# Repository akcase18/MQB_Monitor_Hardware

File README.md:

# Hardware Design for MQB Monitor

This is the PCB used for my software project, MQB Monitor, and enables the software features found in that repository.

This project was fully designed in KiCad, with the intention of using JLCPCB for both PCB manufacturing and assembly.

## Features

This project was designed to be a full plug-and-play compact display that could be used to show configurable information as reported by my car. I wanted installation to be easy and fully reversible, and require little-to-know technical knowledge in order to get it up and running.

To support this goal, this PCB is designed around a 480x320 3.5" LCD panel that supports capacitive touch, fast refresh rates, high-brightess, and is readily available. This allows the screen to be visible in a car in all but direct sunlight, react quickly to new information, and is glass-coated for better durablility and easier use. The PCB attaches directly to the back of the LCD panel (I use double-sided tape) for a secure and very compact package.

It utilizes a 4-wire connection to the car with a custom wiring harness that plugs directly into the OBD2 port. It pulls power, ground, and CAN (CAN high and low) directly from the port. Power is pulled from the ignition source, so the display turns on when the car turns on, turns off when the car turns off, and doesn't pull power while the car is off so there is no extra battey drain.

It also has a USB-C port on-board that can be used for updates and other communication with the MCU.

## Major Components

The full BOM can be found in the KiCad project, as well as in the `bom_production` folder, but the major components used for this are listed below. Please note, this information is only applicable to PCB v5.1.0.

- ESP32-S3-WROOM-1: This is the MCU for the project, and is what actually runs the display. For this board, it is recommended to use N16R8. See below for a more in-depth explanation.
  - There are multiple different flash configurations for this ESP module, indicated using N{X}R{Y}, where X is total flash storage and Y is the amount of PSRAM in the module. On v5.0.2 of this board, only N16R2 was supported because 1) N16 gives you maximum internal flash for logging purposes and 2) R2 uses quad SPI for PSRAM instead of octal SPI (which is used by other R configurations). THe pinout used for that PCB was not compatible with octal SPI PSRAM.
- PAM2804AAB010: LCD backlight driver. Used to control display brightness.
- PLMR54410DBVR: 12v -> 5v switching regulator, helps with overvoltage protection when connected to the car as well.
- AMS1117-3.3L: 5v -> 3.3v LDO, provides steady voltage source for display and MCU.
- SN65HVD230: Automotive CAN transceiver.
- ER-TFT035-6: LCD panel used. This connects to the PCB via 50-pin FPC connector, has a capacitive touch controller (via I2c), and is driven by the MCU using 8-bit parallel.

As mentioned, there are other supporting components used that are listed in the full BOM. There may be alternatives to some of the components on the board, but the components selected were chosen to minimize cost and maximize component availablilty, specifically for using JLCPCB for PCBA.

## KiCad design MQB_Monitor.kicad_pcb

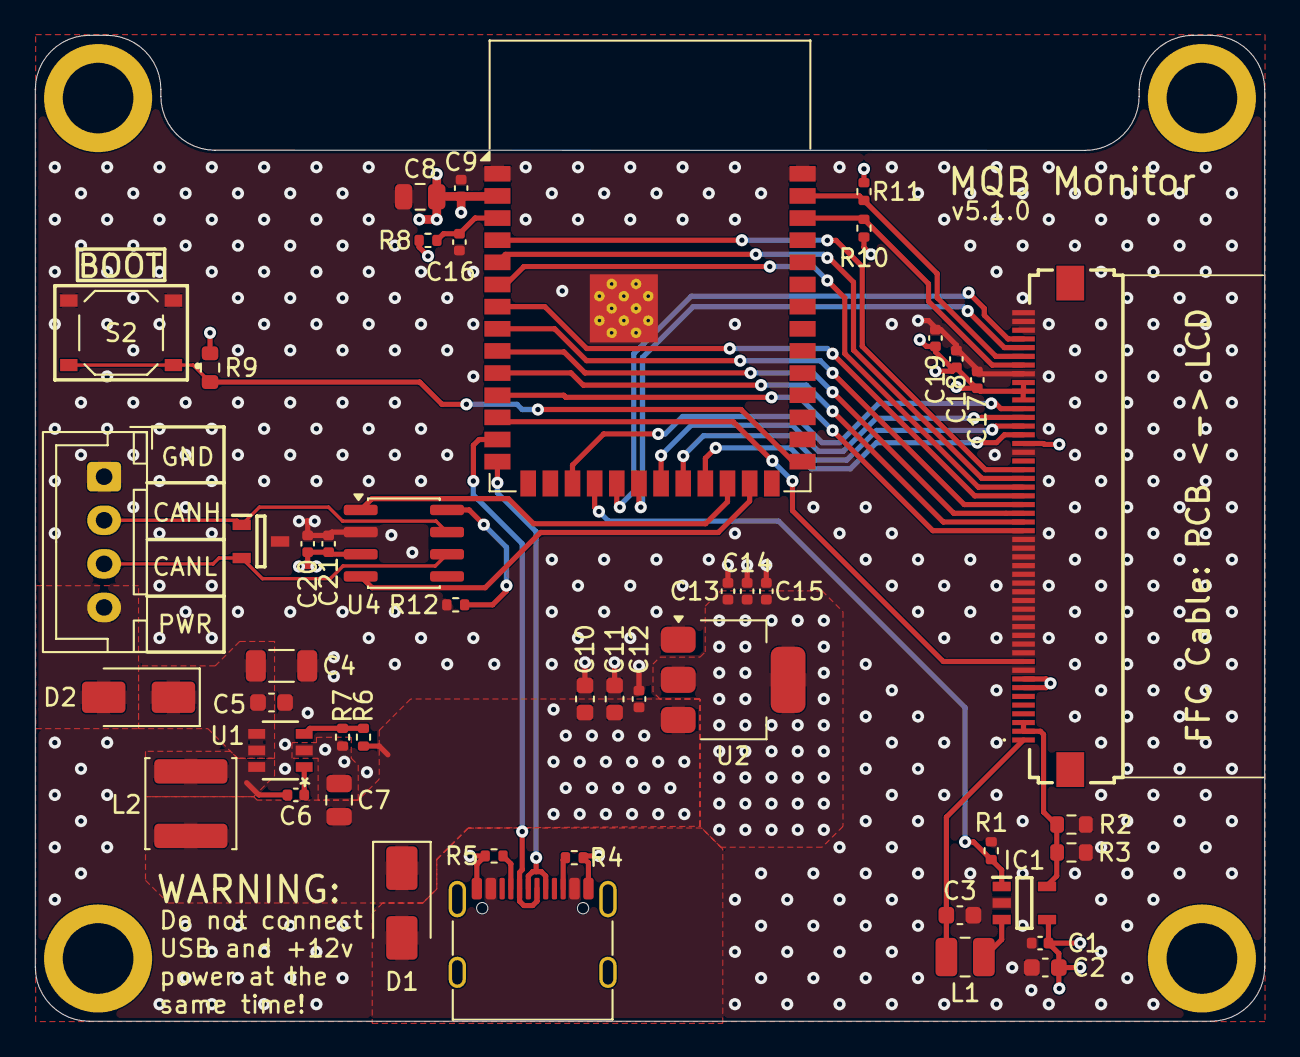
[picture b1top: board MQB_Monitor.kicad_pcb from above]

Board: 4 copper layers, 70.5 x 56.5 mm, 51 parts (0 on the bottom side), 41 nets.

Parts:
C1, C6, C9, C12, C13, C17, C18, C21: 0.1uF; C_0402_1005Metric
C2, C3, C10, C11: 10uF; C_0603_1608Metric
C4: 10uF; C_1206_3216Metric
C5: 0.1uF; C_0603_1608Metric
C7, C8: 22uF; C_0805_2012Metric
C14, C15, C19, C20: 10uF; C_0402_1005Metric
C16: 1uF; C_0402_1005Metric
D1, D2: Diode; D_SMA
D3: PESD1CAN,215; SOT95P230X110-3N
H1, H2, H3, H4: MountingHole; Keystone_24881
IC1: PAM2804AAB010; SOT95P280X100-5N
J1: AFC01-S50FCA-00; AFC01S50FCA00
J2: 4-Pin to Car; JST_XH_B4B-XH-A_1x04_P2.50mm_Vertical
L1: 4.7uH; L_1008_2520Metric
L2: 15uH; L_Changjiang_FNR5040S
R1: 100k; R_0402_1005Metric
R2: 1R; R_0603_1608Metric
R3: 10R; R_0603_1608Metric
R4, R5: 5.1k; R_0402_1005Metric
R6: 51k; R_0402_1005Metric
R7, R8, R10, R11, R12: 10k; R_0402_1005Metric
R9: 1k; R_0603_1608Metric
S2: Push Button; SW_PTS526_SM08_SMTR2_LFS
U1: PLMR54410DBVR; U_SOT-23_TEX
U2: AMS1117-3.3; SOT-223-3_TabPin2
U3: ESP32-S3-WROOM-1
U4: SN65HVD230; SOIC-8_3.9x4.9mm_P1.27mm
USB1: USB-C Port; USB_C_Receptacle_G-Switch_GT-USB-7010ASV

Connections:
+3.3V: C8.1, C9.1, C13.1, C14.1, C15.1, C17.1, C18.1, C19.1, C20.1, C21.1, J1.7, J1.8, J1.35, J1.40, J1.41, J1.42, R8.2, R9.1, R10.1, R11.1, U2.2 (VO), U3.2 (3V3), U4.3 (VCC)
+5V: C1.1, C2.1, C7.1, C10.1, C11.1, C12.1, D1.1 (K), IC1.4 (VIN), L2.1, R6.1, U2.3 (VI)
+12V: C4.1, C5.1, D2.1 (K), U1.4 (EN), U1.5 (VIN)
/12V_Car: D2.2 (A), J2.4
/CAN_RS: R12.1, U4.8 (Rs)
/CB: C6.2, U1.1 (CB)
/ESP_BOOT: R9.2, S2.1, S2.2, U3.27 (IO0)
/ESP_EN: C16.2, R8.1, U3.3 (EN)
/FB: R6.2, R7.1, U1.3 (FB)
/P1_CC1: R5.1, USB1.A5 (CC1)
/P1_CC2: R4.2, USB1.B5 (CC2)
/P1_VBUS: D1.2 (A), USB1.A4 (VBUS), USB1.A9 (VBUS), USB1.B4 (VBUS), USB1.B9 (VBUS)
/SW: C6.1, L2.2, U1.6 (SW)
BL_CTRL: IC1.1 (EN), R1.1, U3.18 (IO10)
CANH: D3.1 (CATHODE_1), J2.2, U4.7 (CANH)
CANL: D3.2 (CATHODE_2), J2.3, U4.6 (CANL)
CAN_RXI: U3.25 (IO48), U4.4 (R)
CAN_TX0: U3.24 (IO47), U4.1 (D)
ESP_USB_N: U3.13 (USB_D-), USB1.A7 (D-), USB1.B7 (D-)
ESP_USB_P: U3.14 (USB_D+), USB1.A6 (D+), USB1.B6 (D+)
GND: C1.2, C2.2, C3.2, C4.2, C5.2, C7.2, C8.2, C9.2, C10.2, C11.2, C12.2, C13.2, C14.2, C15.2, C16.1, C17.2, C18.2, C19.2, C20.2, C21.2, D3.3 (COMMON_CATHODE), IC1.2 (GND), J1.9, J1.11, J1.12, J1.13, J1.14, J1.15, J1.16, J1.17, J1.18, J1.19, J1.20, J1.21, J1.22, J1.23, J1.24, J1.34, J1.43, J1.48, J1.49, J1.50, J2.1, R1.2, R2.2, R3.2, R4.1, R5.2, R7.2, R12.2, S2.3, S2.4, U1.2 (GND), U2.1 (GND), U3.1 (GND), U3.40 (GND), U3.41 (GND), U4.2 (GND), USB1.A1 (GND), USB1.A12 (GND), USB1.B1 (GND), USB1.B12 (GND)
LCD_CS: J1.38, U3.21 (IO13)
LCD_DC: J1.37, U3.22 (IO14)
LCD_RESET: J1.10, U3.12 (IO8)
LCD_TE: J1.39, U3.17 (IO9)
LCD_WR: J1.36, U3.23 (IO21)
LED_A: C3.1, J1.1, L1.2
LED_K: IC1.5 (VOUT/FB), J1.2, J1.3, R2.1, R3.1
unnamed: IC1.3 (SW), L1.1
PARALLEL_0: J1.32, U3.4 (IO4)
PARALLEL_1: J1.31, U3.5 (IO5)
PARALLEL_2: J1.30, U3.6 (IO6)
PARALLEL_3: J1.29, U3.7 (IO7)
PARALLEL_4: J1.28, U3.8 (IO15)
PARALLEL_5: J1.27, U3.9 (IO16)
PARALLEL_6: J1.26, U3.10 (IO17)
PARALLEL_7: J1.25, U3.11 (IO18)
TOUCH_PEN_INT: J1.46, U3.20 (IO12)
TOUCH_RESET: J1.47, U3.19 (IO11)
TOUCH_SCL: J1.44, R10.2, U3.38 (IO2)
TOUCH_SDA: J1.45, R11.2, U3.39 (IO1)

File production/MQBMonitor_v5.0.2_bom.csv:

Designator,Footprint,Quantity,Value,LCSC Part #
"C1, C12, C13, C17, C18, C21, C6, C9",0402,8,0.1uF,C1525
"C10, C11, C2, C3",0603,4,10uF,C96446
"C14, C15, C19, C20",0402,4,10uF,C15525
C16,0402,1,1uF,C52923
C4,1206,1,10uF,C13585
C5,0603,1,0.1uF,C14663
"C7, C8",0805,2,22uF,C45783
"D1, D2",D_SMA,2,Diode,C8678
D3,SOT95P230X110-3N,1,"PESD1CAN,215",C15771
IC1,SOT95P280X100-5N,1,PAM2804AAB010,C71463
J1,AFC01S50FCA00,1,AFC01-S50FCA-00,C262676
J2,JST_XH_B4B-XH-A_1x04_P2.50mm_Vertical,1,4-Pin to Car,N/A
L1,1008,1,4.7uH,C5832360
L2,L_Changjiang_FNR5040S,1,15uH,C167969
R1,0402,1,100k,C25741
"R10, R11, R12, R7, R8",0402,5,10k,C25744
R2,0603,1,1R,C22936
R3,0603,1,10R,C22859
"R4, R5",0402,2,5.1k,C25905
R6,0402,1,51k,C25794
R9,0603,1,1k,C21190
"S1, S2",SW_PTS526_SM08_SMTR2_LFS,2,Push Button,C2689521
U1,U_SOT-23_TEX,1,PLMR54410DBVR,C3200265
U2,SOT-223-3_TabPin2,1,AMS1117-3.3,C6186
U3,ESP32-S3-WROOM-1,1,ESP32-S3-WROOM-1,C2913205
U4,SOIC-8_3.9x4.9mm_P1.27mm,1,SN65HVD230,C12084
USB1,USB_C_Receptacle_G-Switch_GT-USB-7010ASV,1,USB-C Port,C2988369

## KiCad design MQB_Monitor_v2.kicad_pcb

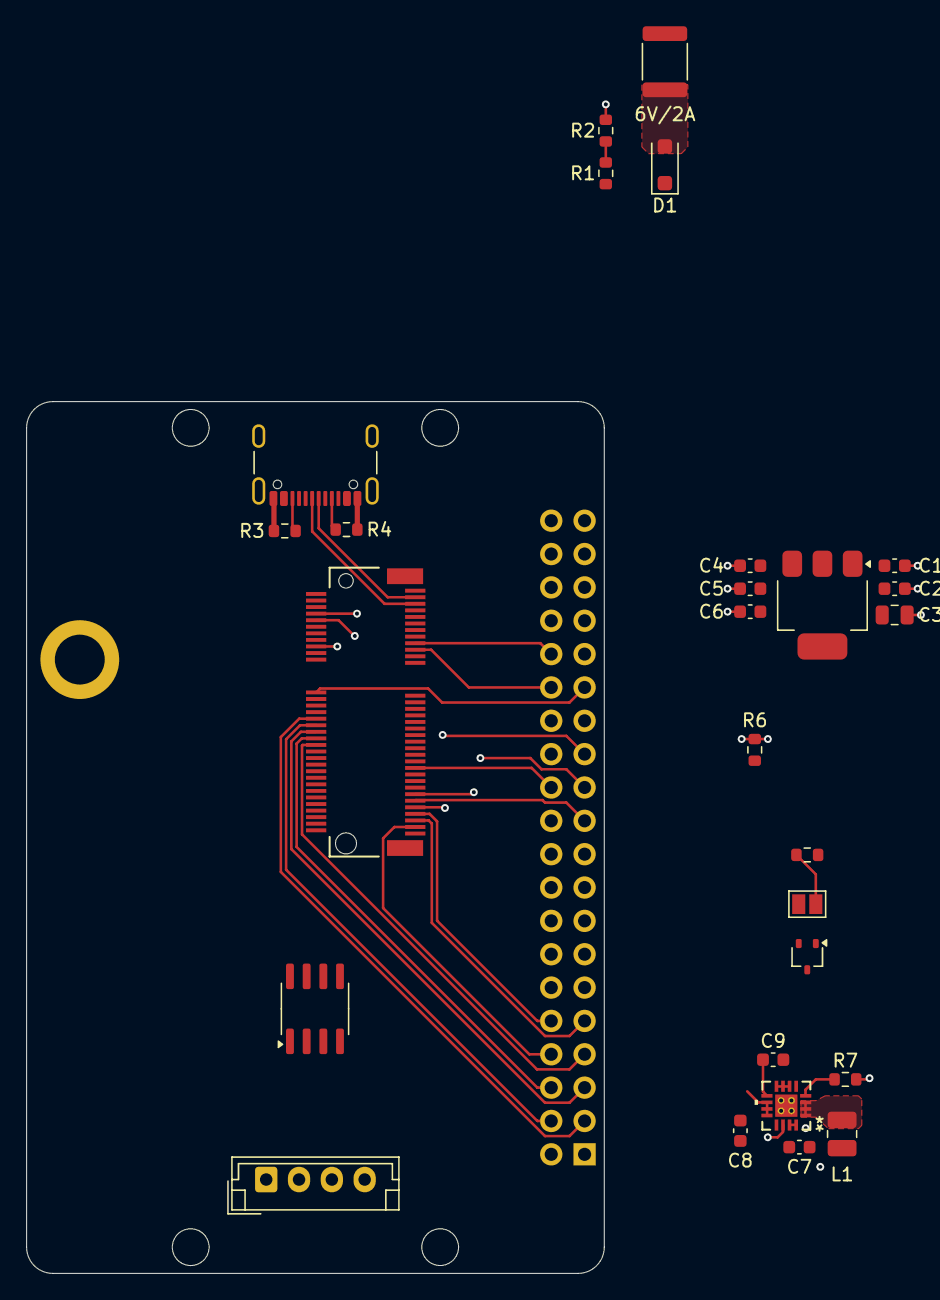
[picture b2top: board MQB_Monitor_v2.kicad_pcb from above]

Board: 4 copper layers, 44.0 x 66.4 mm, 29 parts (1 on the bottom side), 38 nets.

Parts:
C1, C6: 0.1uF; C_0603_1608Metric
C2, C5: 0.22uF; C_0603_1608Metric
C3: 10uF; C_0805_2012Metric
C4: 1uF; C_0603_1608Metric
C7: 22uF; C_0603_1608Metric
C8: 10uF; C_0603_1608Metric
C9: 3.3nF; C_0603_1608Metric
D1: 10V/2A; D_SOD-123F
D2: ESDCAN03-2BWY; SOT-323_SC-70
F1: 6V/2A; Fuse_1812_4532Metric
H1: MM_Standoff; STAND-OFF-REFLOW-M2.5
J1: M.2-CONNECTOR-E
J2: Display Connector; PinSocket_2x20_P2.54mm_Vertical
J3: 4-Pin to Car; JST_EH_B4B-EH-A_1x04_P2.50mm_Vertical
JP2: R_Select; SolderJumper-2_P1.3mm_Open_Pad1.0x1.5mm
L1: 2.2uH; L_1008_2520Metric
P1: USB_C_Plug_USB2.0; USB_C_Receptacle_GCT_USB4105-xx-A_16P_TopMnt_Horizontal
R1, R2, R6: 10K; R_0603_1608Metric
R3, R4: 5.1K; R_0603_1608Metric
R5: 120; R_0603_1608Metric
R7: 100K; R_0603_1608Metric
U1: AP7361C-33E; SOT-223-3_TabPin2
U2: SN65HVD230; SOIC-8_3.9x4.9mm_P1.27mm
U3: TPS62143; RGT16_1P7X1P7

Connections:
+3.3V: C4.1, C5.1, C6.1, J1.2 (3.3V), J1.74 (3.3V), J2.2, J2.26, U1.3 (VO), U2.3 (VCC)
+5V: C1.1, C2.1, C3.1, C7.1, D1.1 (K), J1.9 (USB_VIN), L1.2, R1.1, R7.2, U1.1 (VI), U3.14 (VOS)
+12V: C8.1, J3.1, U3.10 (VIN), U3.11 (VIN), U3.12 (VIN), U3.13 (EN)
BL_CTRL: J1.32 (PWM0), J2.29
CANH: D2.2 (K), J3.3, JP2.2 (B), U2.7 (CANH)
CANL: D2.1 (K), J3.2, R5.2, U2.6 (CANL)
CAN_RXI: J1.41 (CAN-RX), U2.4 (R)
CAN_TX0: J1.43 (CAN-TX), U2.1 (D)
D0: J1.40 (G0/BUS0), J2.3
D1: J1.42 (G1/BUS1), J2.4
D2: J1.44 (G2/BUS2), J2.5
D3: J1.46 (G3/BUS3), J2.6
D4: J1.48 (G4/BUS4), J2.7
D5: J1.73 (G5/BUS5), J2.8
D6: J1.71 (G6/BUS6), J2.9
D7: J1.69 (G7/BUS7), J2.10
D/C: J1.18 (D1/CAM_TRIG), J2.25
GND: C1.2, C2.2, C3.2, C4.2, C5.2, C6.2, C7.2, C8.2, C9.2, D2.3 (A), H1.1, J1.1 (GND), J1.7 (GND), J1.33 (GND), J1.36 (GND), J1.39 (GND), J1.45 (GND), J1.75 (GND), J2.1, J2.40, J3.4, P1.A1 (GND), P1.A12 (GND), P1.B1 (GND), P1.B12 (GND), R2.2, R3.1, R4.2, R6.2, U1.2 (GND), U2.2 (GND), U3.6 (GND), U3.7 (FSW), U3.8 (DEF), U3.15 (GND), U3.16 (GND), U3.17 (GND), U3.V
LCD_~CS: J1.10 (D0), J2.23
unnamed: D1.2 (A), F1.2
unnamed: JP2.1 (A), R5.1
unnamed: L1.1, U3.1 (SW), U3.2 (SW), U3.3 (SW)
unnamed: P1.A5 (CC), R4.1
unnamed: P1.B5 (VCONN), R3.2
unnamed: R6.1, U2.8 (Rs)
unnamed: R7.1, U3.4 (PG)
unnamed: C9.1, U3.9 (SS/TR)
SCL: J1.67 (G8), J2.33
SDI: J1.8 (G11), J2.34
SDO: J1.17 (TX1), J2.32
TS_~CS: J1.19 (RX1), J2.30
USB_N: J1.5 (USB_D-), P1.A7 (D-)
USB_P: J1.3 (USB_D+), P1.A6 (D+)
VIN/3: J1.49 (BATT_VIN/3), R1.2, R2.1
V_USB: F1.1, P1.A4 (VBUS), P1.A9 (VBUS), P1.B4 (VBUS), P1.B9 (VBUS)
~PEN_INT: J1.63 (G10/ADC_D+/CAM_VSYNC), J2.31
~RST_DISP: J1.65 (G9/ADC_D-/CAM_HSYNC), J2.21
~WR_DISP: J1.55 (SPI_~CS), J2.24
